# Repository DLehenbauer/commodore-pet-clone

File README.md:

## PET Clone

Open hardware clone of the Commodore CBM/PET using modern parts.
Some assembly required.  :-)

## Status

Working prototype.  PCB and SMT manufacturing files are [here](https://github.com/DLehenbauer/commodore-pet-clone/tree/main/hw/Mainboard/production).

## About

This open hardware CBM/PET clone can be used in two ways:

1. By itself with an HDMI display and USB keyboard
2. As a mainboard replacement to repair/enhance a vintage CBM/PET

You can also do both at once, as shown in the image below:

## Design

The following block diagram provides an overview of the system architecture:

Here are the highlights:

* CPU and I/O are similar to the original Commodore design, using the 6502, PIA, and VIA.
* Main RAM, Display RAM and ROM are combined on a single 128K SRAM.
  * On POR the MCU initializes $9000-FFFF with the user's selected ROM set
  * After initialization, $9000-FFFF is write protected.
* Timing, address decoding, and native PET video are consolidated on a small FPGA.
* The MCU reads display RAM and mirrors the PET video to HDMI (via bit-banged DVI)
* The MCU also reports USB keyboard input to the FPGA
  * The FPGA intercepts reads from $E812 to inject USB key input as-needed
  * When no USB keys are pressed, the read passes through to PIA1.

## Contributing

Collaborators warmly appreciated (see [Issues](https://github.com/DLehenbauer/commodore-pet-clone/issues)).

## License

This project is public domain under the CC0-1.0 license, exempting portions incorporated
from other open source projects as noted [here](NOTICE.md) and in the source code.

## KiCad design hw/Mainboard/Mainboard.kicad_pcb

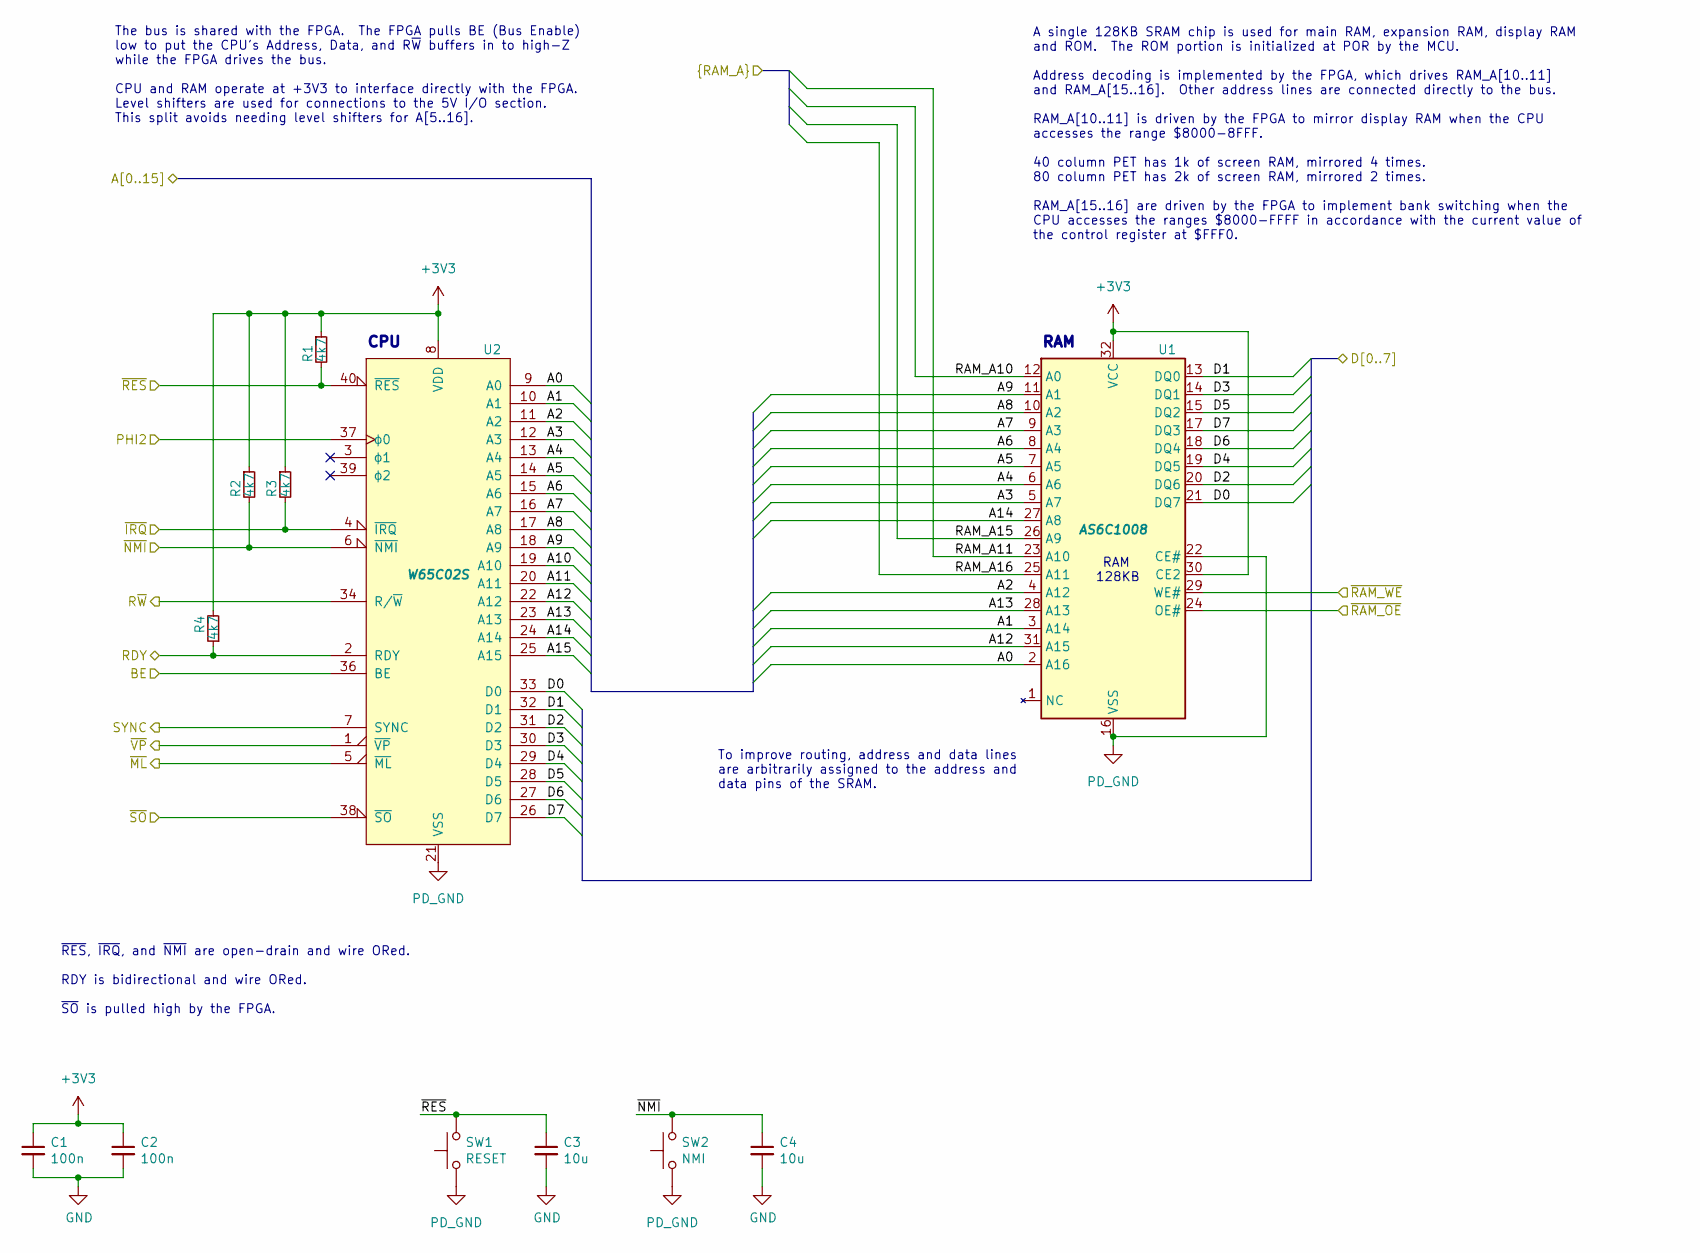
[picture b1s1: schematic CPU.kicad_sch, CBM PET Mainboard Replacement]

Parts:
C1, C2: 100n; C_0402_1005Metric; LCSC C307331
C3, C4: 10u; C_0603_1608Metric; LCSC C96446
R1, R2, R3, R4: 4k7; R_0402_1005Metric; LCSC C25900
SW1: RESET; SW-TH_L6.0-W3.5-P6.50; MOUSER 611-PTS636SK43LFS
SW2: NMI; SW-TH_L6.0-W3.5-P6.50; MOUSER 611-PTS636SK43LFS
U1: AS6C1008; DIP-32_W15.24mm_Socket; MOUSER 913-AS6C1008-55PCN,649-DILB32P223TLF
U2: W65C02S; DIP-40_W15.24mm_Socket; MOUSER 955-W65C02S6TPG-14,571-1-2199299-5

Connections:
+3V3: C1.1, C2.1, R1.1, R2.1, R3.1, R4.2, U1.30 (CE2), U1.32 (VCC), U2.8 (VDD); also elsewhere on the board
/CPU \ RAM/A0: U1.2 (A16), U2.9 (A0); also elsewhere on the board
/CPU \ RAM/A1: U1.3 (A14), U2.10 (A1); also elsewhere on the board
/CPU \ RAM/A2: U1.4 (A12), U2.11 (A2); also elsewhere on the board
/CPU \ RAM/A3: U1.5 (A7), U2.12 (A3); also elsewhere on the board
/CPU \ RAM/A4: U1.6 (A6), U2.13 (A4); also elsewhere on the board
/CPU \ RAM/A5: U1.7 (A5), U2.14 (A5); also elsewhere on the board
/CPU \ RAM/A6: U1.8 (A4), U2.15 (A6); also elsewhere on the board
/CPU \ RAM/A7: U1.9 (A3), U2.16 (A7); also elsewhere on the board
/CPU \ RAM/A8: U1.10 (A2), U2.17 (A8); also elsewhere on the board
/CPU \ RAM/A9: U1.11 (A1), U2.18 (A9); also elsewhere on the board
/CPU \ RAM/A10: U2.19 (A10); also elsewhere on the board
/CPU \ RAM/A11: U2.20 (A11); also elsewhere on the board
/CPU \ RAM/A12: U1.31 (A15), U2.22 (A12); also elsewhere on the board
/CPU \ RAM/A13: U1.28 (A13), U2.23 (A13); also elsewhere on the board
/CPU \ RAM/A14: U1.27 (A8), U2.24 (A14); also elsewhere on the board
/CPU \ RAM/A15: U2.25 (A15); also elsewhere on the board
/CPU \ RAM/D0: U1.21 (DQ7), U2.33 (D0); also elsewhere on the board
/CPU \ RAM/D1: U1.13 (DQ0), U2.32 (D1); also elsewhere on the board
/CPU \ RAM/D2: U1.20 (DQ6), U2.31 (D2); also elsewhere on the board
/CPU \ RAM/D3: U1.14 (DQ1), U2.30 (D3); also elsewhere on the board
/CPU \ RAM/D4: U1.19 (DQ5), U2.29 (D4); also elsewhere on the board
/CPU \ RAM/D5: U1.15 (DQ2), U2.28 (D5); also elsewhere on the board
/CPU \ RAM/D6: U1.18 (DQ4), U2.27 (D6); also elsewhere on the board
/CPU \ RAM/D7: U1.17 (DQ3), U2.26 (D7); also elsewhere on the board
/CPU \ RAM/RAM_A10: U1.12 (A0); also elsewhere on the board
/CPU \ RAM/RAM_A11: U1.23 (A10); also elsewhere on the board
/CPU \ RAM/RAM_A15: U1.26 (A9); also elsewhere on the board
/CPU \ RAM/RAM_A16: U1.25 (A11); also elsewhere on the board
/CPU \ RAM/~NMI: C4.1, R2.2, SW2.2, U2.6 (~NMI); also elsewhere on the board
/CPU \ RAM/~RES: C3.1, R1.2, SW1.2, U2.40 (~RES); also elsewhere on the board
/MAGIC/FPGA/BE: U2.36 (BE); also elsewhere on the board
/MAGIC/FPGA/RDY: R4.1, U2.2 (RDY); also elsewhere on the board
/MAGIC/FPGA/SYNC: U2.7 (SYNC); also elsewhere on the board
/MAGIC/FPGA/~IRQ: R3.2, U2.4 (~IRQ); also elsewhere on the board
/MAGIC/FPGA/~ML: U2.5 (~ML); also elsewhere on the board
/MAGIC/FPGA/~RAM_OE: U1.24 (OE#); also elsewhere on the board
/MAGIC/FPGA/~RAM_WE: U1.29 (WE#); also elsewhere on the board
/MAGIC/FPGA/~SO: U2.38 (~SO); also elsewhere on the board
/MAGIC/FPGA/~VP: U2.1 (~VP); also elsewhere on the board
/MAGIC/PHI2: U2.37 (ϕ0); also elsewhere on the board
/MAGIC/R~W: U2.34 (R/~W); also elsewhere on the board
GND: C1.2, C2.2, C3.2, C4.2; also elsewhere on the board
PD_GND: SW1.1, SW2.1, U1.16 (VSS), U1.22 (CE#), U2.21 (VSS); also elsewhere on the board

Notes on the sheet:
RAM
A single 128KB SRAM chip is used for main RAM, expansion RAM, display RAM and ROM. The ROM portion is initialized at POR by the MCU. Address decoding is implemented by the FPGA, which drives RAM_A[10..11] and RAM_A[15..16]. Other address lines are connected directly to the bus. RAM_A[10..11] is dri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
To improve routing, address and data lines are arbitrarily assigned to the address and data pins of the SRAM.
~{RES}, ~{IRQ}, and ~{NMI} are open-drain and wire ORed. RDY is bidirectional and wire ORed. ~{SO} is pulled high by the FPGA.
RAM 128KB
CPU
The bus is shared with the FPGA. The FPGA pulls BE (Bus Enable) low to put the CPU's Address, Data, and R~{W} buffers in to high-Z while the FPGA drives the bus. CPU and RAM operate at +3V3 to interface directly with the FPGA. Level shifters are used for connections to the 5V I/O section. This spli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

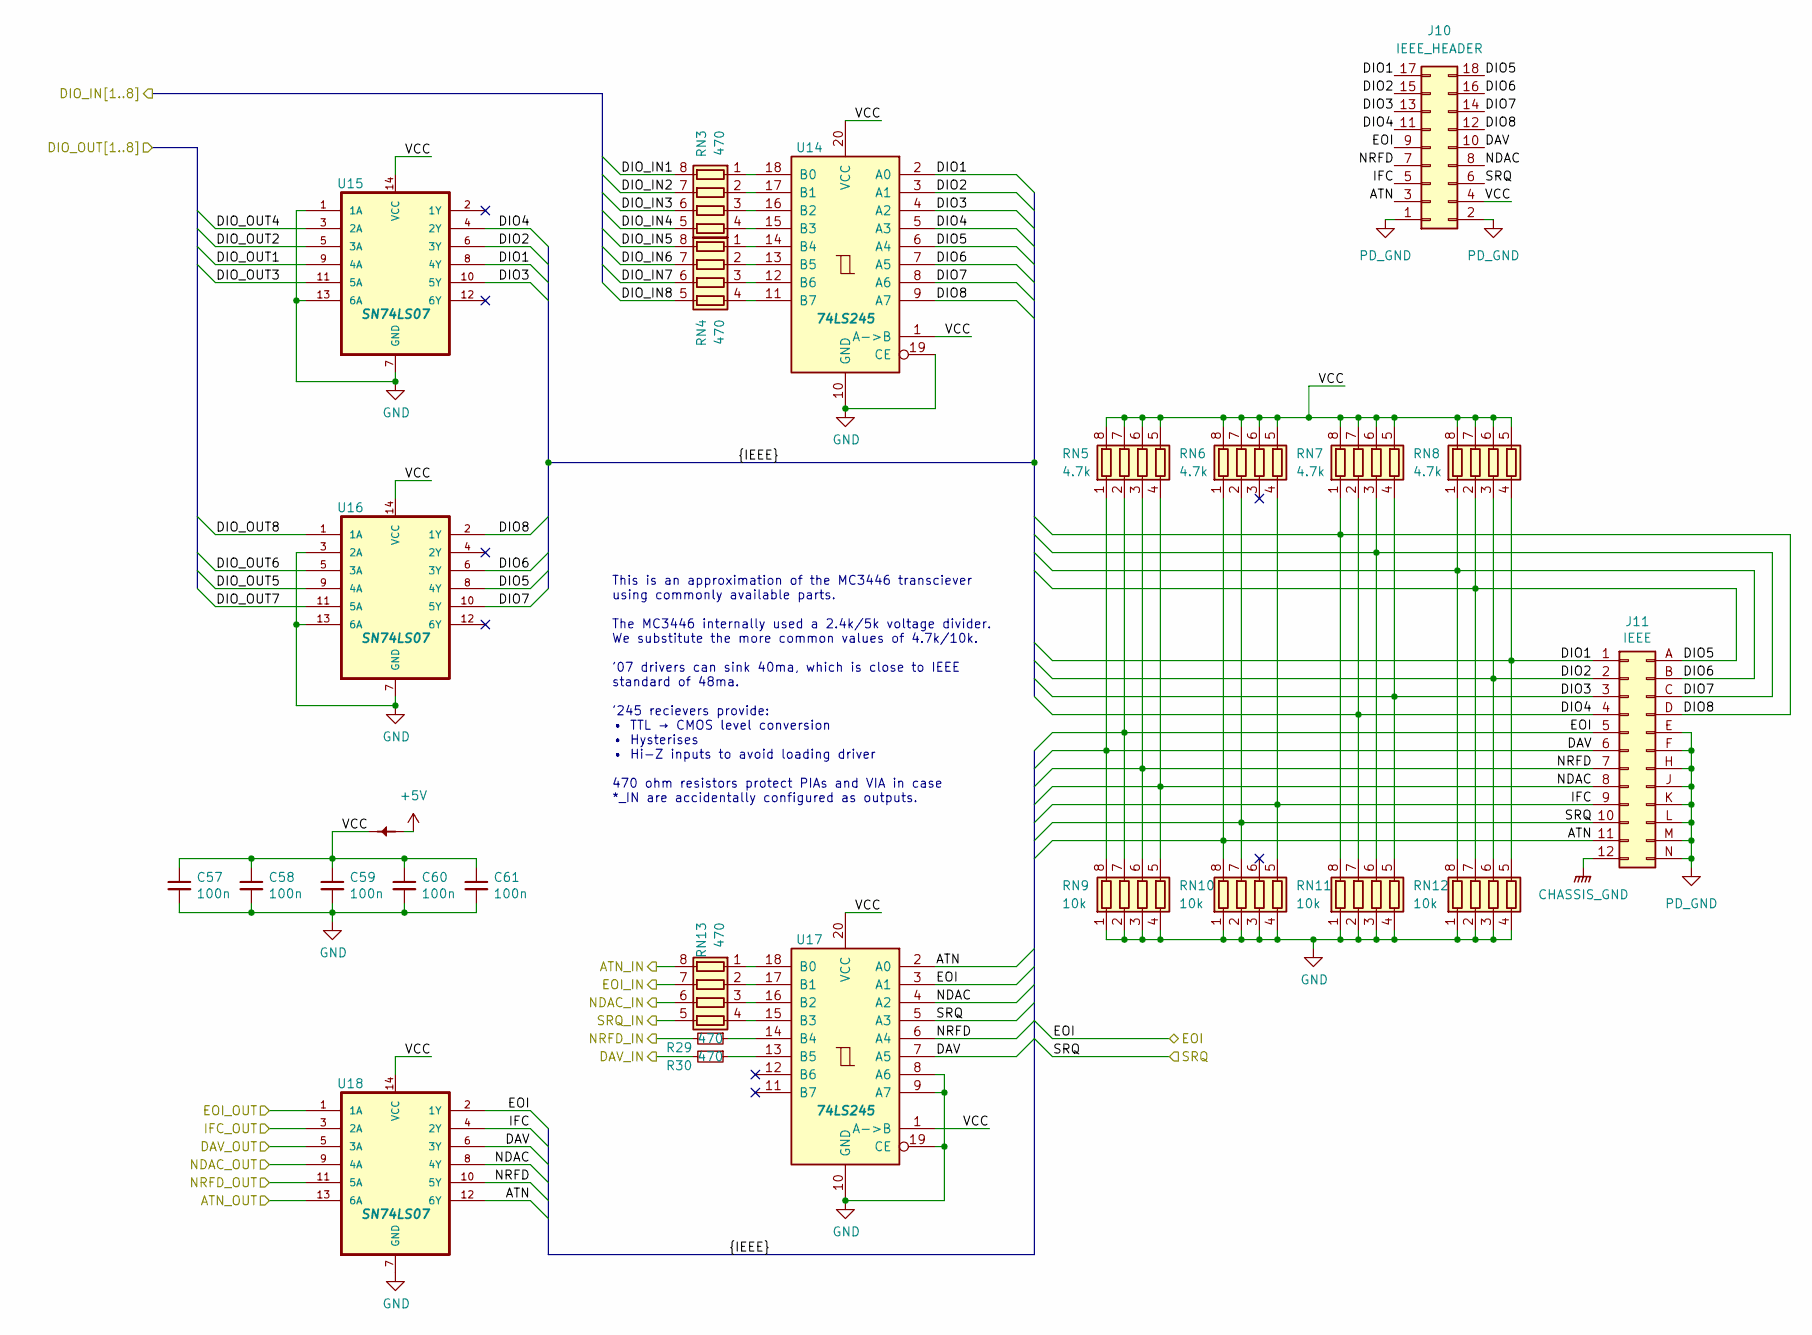
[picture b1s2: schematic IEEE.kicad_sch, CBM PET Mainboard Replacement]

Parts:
C57, C58, C59, C60, C61: 100n; C_0402_1005Metric; LCSC C307331
J10: IEEE_HEADER; PinHeader_2x09_P2.54mm_Vertical; MOUSER 649-1012938195002BLF
J11: IEEE; CBM_PET_IEEE_EDGE_CON_24P
PT36: PowerTie_2; NetTie-2_SMD_Pad_1.6_to_0.4mm
R29, R30: 470; R_0402_1005Metric; LCSC C25117
RN3, RN4, RN13: 470; R_Array_Convex_4x0603; LCSC C25510
RN5, RN6, RN7, RN8: 4.7k; R_Array_Convex_4x0603; LCSC C1980
RN9, RN10, RN11, RN12: 10k; R_Array_Convex_4x0603; LCSC C29718
U14, U17: 74LS245; SOIC-20W_7.5x12.8mm_P1.27mm; LCSC C129580
U15, U16, U18: SN74LS07; SOIC-14_3.9x8.7mm_P1.27mm; LCSC C513513

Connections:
+5V: PT36.1; also elsewhere on the board
/IEEE/ATN: J10.3, J11.11 (ATN), RN6.1 (R1.1), RN10.8 (R1.2), U17.2 (A0), U18.12 (6Y)
/IEEE/ATN_IN: RN13.8 (R1.2); also elsewhere on the board
/IEEE/ATN_OUT: U18.13 (6A); also elsewhere on the board
/IEEE/DAV: J10.10, J11.6 (DAV), RN5.1 (R1.1), RN9.8 (R1.2), U17.7 (A5), U18.6 (3Y)
/IEEE/DAV_IN: R30.2; also elsewhere on the board
/IEEE/DAV_OUT: U18.5 (3A); also elsewhere on the board
/IEEE/DIO1: J10.17, J11.1 (DIO1), RN8.4 (R4.1), RN12.5 (R4.2), U14.2 (A0), U15.8 (4Y)
/IEEE/DIO2: J10.15, J11.2 (DIO2), RN8.3 (R3.1), RN12.6 (R3.2), U14.3 (A1), U15.6 (3Y)
/IEEE/DIO3: J10.13, J11.3 (DIO3), RN7.4 (R4.1), RN11.5 (R4.2), U14.4 (A2), U15.10 (5Y)
/IEEE/DIO4: J10.11, J11.4 (DIO4), RN7.2 (R2.1), RN11.7 (R2.2), U14.5 (A3), U15.4 (2Y)
/IEEE/DIO5: J10.18, J11.A (DIO5), RN8.2 (R2.1), RN12.7 (R2.2), U14.6 (A4), U16.8 (4Y)
/IEEE/DIO6: J10.16, J11.B (DIO6), RN8.1 (R1.1), RN12.8 (R1.2), U14.7 (A5), U16.6 (3Y)
/IEEE/DIO7: J10.14, J11.C (DIO7), RN7.3 (R3.1), RN11.6 (R3.2), U14.8 (A6), U16.10 (5Y)
/IEEE/DIO8: J10.12, J11.D (DIO8), RN7.1 (R1.1), RN11.8 (R1.2), U14.9 (A7), U16.2 (1Y)
/IEEE/DIO_IN1: RN3.8 (R1.2); also elsewhere on the board
/IEEE/DIO_IN2: RN3.7 (R2.2); also elsewhere on the board
/IEEE/DIO_IN3: RN3.6 (R3.2); also elsewhere on the board
/IEEE/DIO_IN4: RN3.5 (R4.2); also elsewhere on the board
/IEEE/DIO_IN5: RN4.8 (R1.2); also elsewhere on the board
/IEEE/DIO_IN6: RN4.7 (R2.2); also elsewhere on the board
/IEEE/DIO_IN7: RN4.6 (R3.2); also elsewhere on the board
/IEEE/DIO_IN8: RN4.5 (R4.2); also elsewhere on the board
/IEEE/DIO_OUT1: U15.9 (4A); also elsewhere on the board
/IEEE/DIO_OUT2: U15.5 (3A); also elsewhere on the board
/IEEE/DIO_OUT3: U15.11 (5A); also elsewhere on the board
/IEEE/DIO_OUT4: U15.3 (2A); also elsewhere on the board
/IEEE/DIO_OUT5: U16.9 (4A); also elsewhere on the board
/IEEE/DIO_OUT6: U16.5 (3A); also elsewhere on the board
/IEEE/DIO_OUT7: U16.11 (5A); also elsewhere on the board
/IEEE/DIO_OUT8: U16.1 (1A); also elsewhere on the board
/IEEE/EOI: J10.9, J11.5 (EOI), RN5.2 (R2.1), RN9.7 (R2.2), U17.3 (A1), U18.2 (1Y); also elsewhere on the board
/IEEE/EOI_IN: RN13.7 (R2.2); also elsewhere on the board
/IEEE/EOI_OUT: U18.1 (1A); also elsewhere on the board
/IEEE/IFC: J10.5, J11.9 (IFC), RN6.4 (R4.1), RN10.5 (R4.2), U18.4 (2Y)
/IEEE/IFC_OUT: U18.3 (2A); also elsewhere on the board
/IEEE/NDAC: J10.8, J11.8 (NDAC), RN5.4 (R4.1), RN9.5 (R4.2), U17.4 (A2), U18.8 (4Y)
/IEEE/NDAC_IN: RN13.6 (R3.2); also elsewhere on the board
/IEEE/NDAC_OUT: U18.9 (4A); also elsewhere on the board
/IEEE/NRFD: J10.7, J11.7 (NRFD), RN5.3 (R3.1), RN9.6 (R3.2), U17.6 (A4), U18.10 (5Y)
/IEEE/NRFD_IN: R29.2; also elsewhere on the board
/IEEE/NRFD_OUT: U18.11 (5A); also elsewhere on the board
/IEEE/SRQ: J10.6, J11.10 (SRQ), RN6.2 (R2.1), RN10.7 (R2.2), U17.5 (A3); also elsewhere on the board
/IEEE/SRQ_IN: RN13.5 (R4.2); also elsewhere on the board
/IEEE/VCC: C57.1, C58.1, C59.1, C60.1, C61.1, J10.4, PT36.2, RN5.5 (R4.2), RN5.6 (R3.2), RN5.7 (R2.2), RN5.8 (R1.2), RN6.5 (R4.2), RN6.6 (R3.2), RN6.7 (R2.2), RN6.8 (R1.2), RN7.5 (R4.2), RN7.6 (R3.2), RN7.7 (R2.2), RN7.8 (R1.2), RN8.5 (R4.2), RN8.6 (R3.2), RN8.7 (R2.2), RN8.8 (R1.2), U14.1 (A->B), U14.20 (VCC), U15.14 (VCC), U16.14 (VCC), U17.1 (A->B), U17.20 (VCC), U18.14 (VCC)
CHASSIS_GND: J11.12 (GND); also elsewhere on the board
GND: C57.2, C58.2, C59.2, C60.2, C61.2, RN9.1 (R1.1), RN9.2 (R2.1), RN9.3 (R3.1), RN9.4 (R4.1), RN10.1 (R1.1), RN10.2 (R2.1), RN10.3 (R3.1), RN10.4 (R4.1), RN11.1 (R1.1), RN11.2 (R2.1), RN11.3 (R3.1), RN11.4 (R4.1), RN12.1 (R1.1), RN12.2 (R2.1), RN12.3 (R3.1), RN12.4 (R4.1), U14.10 (GND), U14.19 (CE), U15.1 (1A), U15.7 (GND), U15.13 (6A), U16.3 (2A), U16.7 (GND), U16.13 (6A), U17.8 (A6), U17.9 (A7), U17.10 (GND), U17.19 (CE), U18.7 (GND); also elsewhere on the board
unnamed: R29.1, U17.14 (B4)
unnamed: R30.1, U17.13 (B5)
unnamed: RN3.1 (R1.1), U14.18 (B0)
unnamed: RN3.2 (R2.1), U14.17 (B1)
unnamed: RN3.3 (R3.1), U14.16 (B2)
unnamed: RN3.4 (R4.1), U14.15 (B3)
unnamed: RN4.1 (R1.1), U14.14 (B4)
unnamed: RN4.2 (R2.1), U14.13 (B5)
unnamed: RN4.3 (R3.1), U14.12 (B6)
unnamed: RN4.4 (R4.1), U14.11 (B7)
unnamed: RN13.1 (R1.1), U17.18 (B0)
unnamed: RN13.2 (R2.1), U17.17 (B1)
unnamed: RN13.3 (R3.1), U17.16 (B2)
unnamed: RN13.4 (R4.1), U17.15 (B3)
PD_GND: J10.1, J10.2, J11.E (GND), J11.F (GND), J11.H (GND), J11.J (GND), J11.K (GND), J11.L (GND), J11.M (GND), J11.N (GND); also elsewhere on the board

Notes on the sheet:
This is an approximation of the MC3446 transciever using commonly available parts. The MC3446 internally used a 2.4k/5k voltage divider. We substitute the more common values of 4.7k/10k. '07 drivers can sink 40ma, which is close to IEEE standard of 48ma. '245 recievers provide: • TTL → CMOS level c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

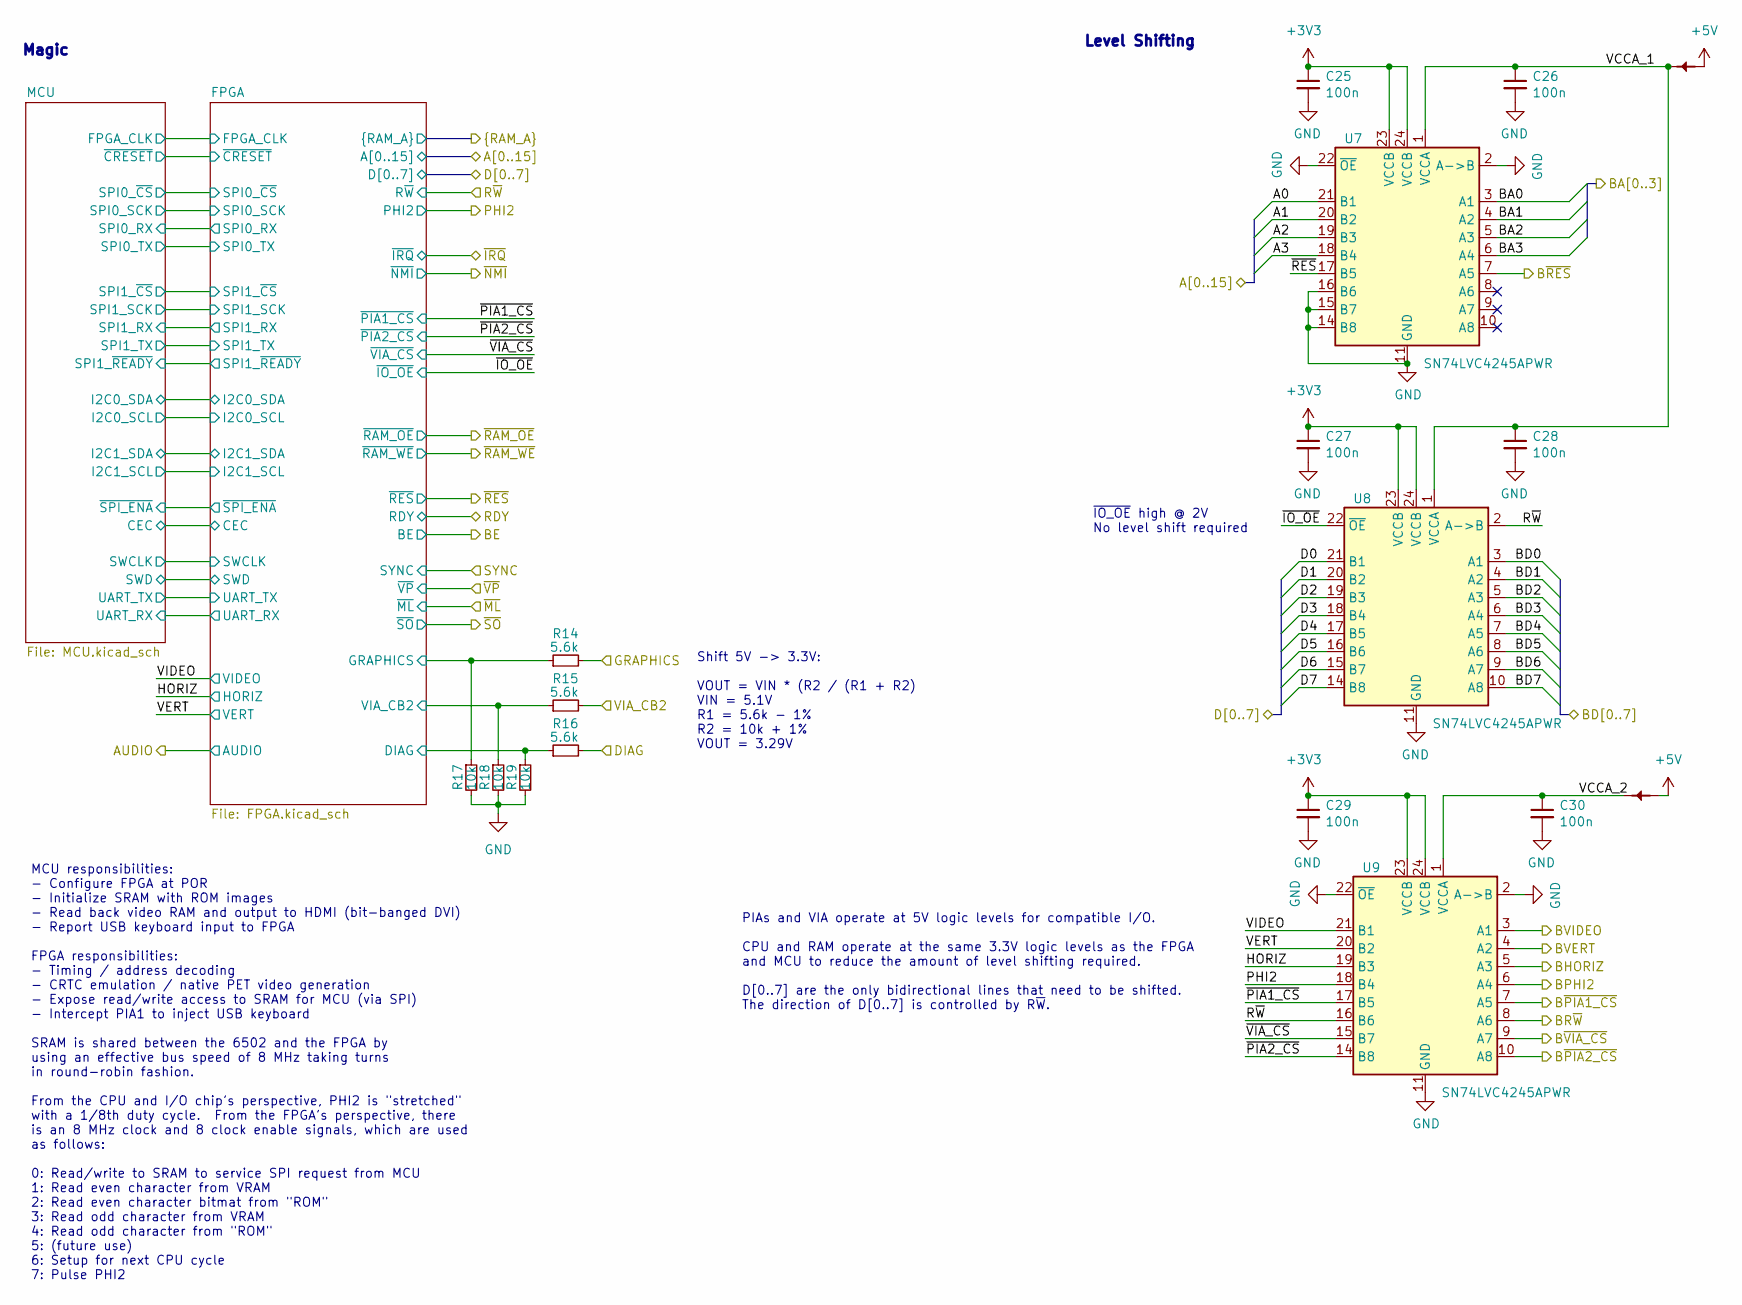
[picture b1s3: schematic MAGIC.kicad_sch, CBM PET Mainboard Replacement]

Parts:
C25, C26, C27, C28, C29, C30: 100n; C_0402_1005Metric; LCSC C307331
PT13, PT14: PowerTie_2; NetTie-2_SMD_Pad_1.6_to_0.4mm
R14, R15, R16: 5.6k; R_0402_1005Metric; LCSC C25908
R17, R18, R19: 10k; R_0402_1005Metric; LCSC C25744
U7, U8, U9: SN74LVC4245APWR; TSSOP-24_4.4x7.8mm_P0.65mm; LCSC C7859

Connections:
+3V3: C25.1, C27.1, C29.1, U7.23 (VCCB), U7.24 (VCCB), U8.23 (VCCB), U8.24 (VCCB), U9.23 (VCCB), U9.24 (VCCB); also elsewhere on the board
+5V: PT13.1, PT14.1; also elsewhere on the board
/CPU \ RAM/A0: U7.21 (B1); also elsewhere on the board
/CPU \ RAM/A1: U7.20 (B2); also elsewhere on the board
/CPU \ RAM/A2: U7.19 (B3); also elsewhere on the board
/CPU \ RAM/A3: U7.18 (B4); also elsewhere on the board
/CPU \ RAM/D0: U8.21 (B1); also elsewhere on the board
/CPU \ RAM/D1: U8.20 (B2); also elsewhere on the board
/CPU \ RAM/D2: U8.19 (B3); also elsewhere on the board
/CPU \ RAM/D3: U8.18 (B4); also elsewhere on the board
/CPU \ RAM/D4: U8.17 (B5); also elsewhere on the board
/CPU \ RAM/D5: U8.16 (B6); also elsewhere on the board
/CPU \ RAM/D6: U8.15 (B7); also elsewhere on the board
/CPU \ RAM/D7: U8.14 (B8); also elsewhere on the board
/CPU \ RAM/~RES: U7.17 (B5); also elsewhere on the board
/IEEE/IFC_OUT: U7.7 (A5); also elsewhere on the board
/IO/BA0: U7.3 (A1); also elsewhere on the board
/IO/BA1: U7.4 (A2); also elsewhere on the board
/IO/BA2: U7.5 (A3); also elsewhere on the board
/IO/BA3: U7.6 (A4); also elsewhere on the board
/IO/BD0: U8.3 (A1); also elsewhere on the board
/IO/BD1: U8.4 (A2); also elsewhere on the board
/IO/BD2: U8.5 (A3); also elsewhere on the board
/IO/BD3: U8.6 (A4); also elsewhere on the board
/IO/BD4: U8.7 (A5); also elsewhere on the board
/IO/BD5: U8.8 (A6); also elsewhere on the board
/IO/BD6: U8.9 (A7); also elsewhere on the board
/IO/BD7: U8.10 (A8); also elsewhere on the board
/IO/BPHI2: U9.6 (A4); also elsewhere on the board
/IO/BR~W: U9.8 (A6); also elsewhere on the board
/IO/BVERT: U9.4 (A2); also elsewhere on the board
/IO/B~PIA1_CS: U9.7 (A5); also elsewhere on the board
/IO/B~PIA2_CS: U9.10 (A8); also elsewhere on the board
/IO/B~VIA_CS: U9.9 (A7); also elsewhere on the board
/IO/DIAG: R16.2; also elsewhere on the board
/IO/GRAPHIC: R14.2; also elsewhere on the board
/IO/VIA_CB2: R15.2; also elsewhere on the board
/MAGIC/BHORIZ: U9.5 (A3); also elsewhere on the board
/MAGIC/BVIDEO: U9.3 (A1); also elsewhere on the board
/MAGIC/FPGA/DIAG: R16.1, R19.1; also elsewhere on the board
/MAGIC/FPGA/GRAPHICS: R14.1, R17.1; also elsewhere on the board
/MAGIC/FPGA/VIA_CB2: R15.1, R18.1; also elsewhere on the board
/MAGIC/HORIZ: U9.19 (B3); also elsewhere on the board
/MAGIC/PHI2: U9.18 (B4); also elsewhere on the board
/MAGIC/R~W: U8.2 (A->B), U9.16 (B6); also elsewhere on the board
/MAGIC/VCCA_1: C26.1, C28.1, PT13.2, U7.1 (VCCA), U8.1 (VCCA)
/MAGIC/VCCA_2: C30.1, PT14.2, U9.1 (VCCA)
/MAGIC/VERT: U9.20 (B2); also elsewhere on the board
/MAGIC/VIDEO: U9.21 (B1); also elsewhere on the board
/MAGIC/~IO_OE: U8.22 (~OE); also elsewhere on the board
/MAGIC/~PIA1_CS: U9.17 (B5); also elsewhere on the board
/MAGIC/~PIA2_CS: U9.14 (B8); also elsewhere on the board
/MAGIC/~VIA_CS: U9.15 (B7); also elsewhere on the board
GND: C25.2, C26.2, C27.2, C28.2, C29.2, C30.2, R17.2, R18.2, R19.2, U7.2 (A->B), U7.11 (GND), U7.12 (GND), U7.13 (GND), U7.14 (B8), U7.15 (B7), U7.16 (B6), U7.22 (~OE), U8.11 (GND), U8.12 (GND), U8.13 (GND), U9.2 (A->B), U9.11 (GND), U9.12 (GND), U9.13 (GND), U9.22 (~OE); also elsewhere on the board

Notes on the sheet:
PIAs and VIA operate at 5V logic levels for compatible I/O. CPU and RAM operate at the same 3.3V logic levels as the FPGA and MCU to reduce the amount of level shifting required. D[0..7] are the only bidirectional lines that need to be shifted. The direction of D[0..7] is controlled by R~{W}.
Level Shifting
Magic
MCU responsibilities: - Configure FPGA at POR - Initialize SRAM with ROM images - Read back video RAM and output to HDMI (bit-banged DVI) - Report USB keyboard input to FPGA FPGA responsibilities: - Timing / address decoding - CRTC emulation / native PET video generation - Expose read/write access 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
~{IO_OE} high @ 2V No level shift required
Shift 5V -> 3.3V: VOUT = VIN * (R2 / (R1 + R2) VIN = 5.1V R1 = 5.6k - 1% R2 = 10k + 1% VOUT = 3.29V

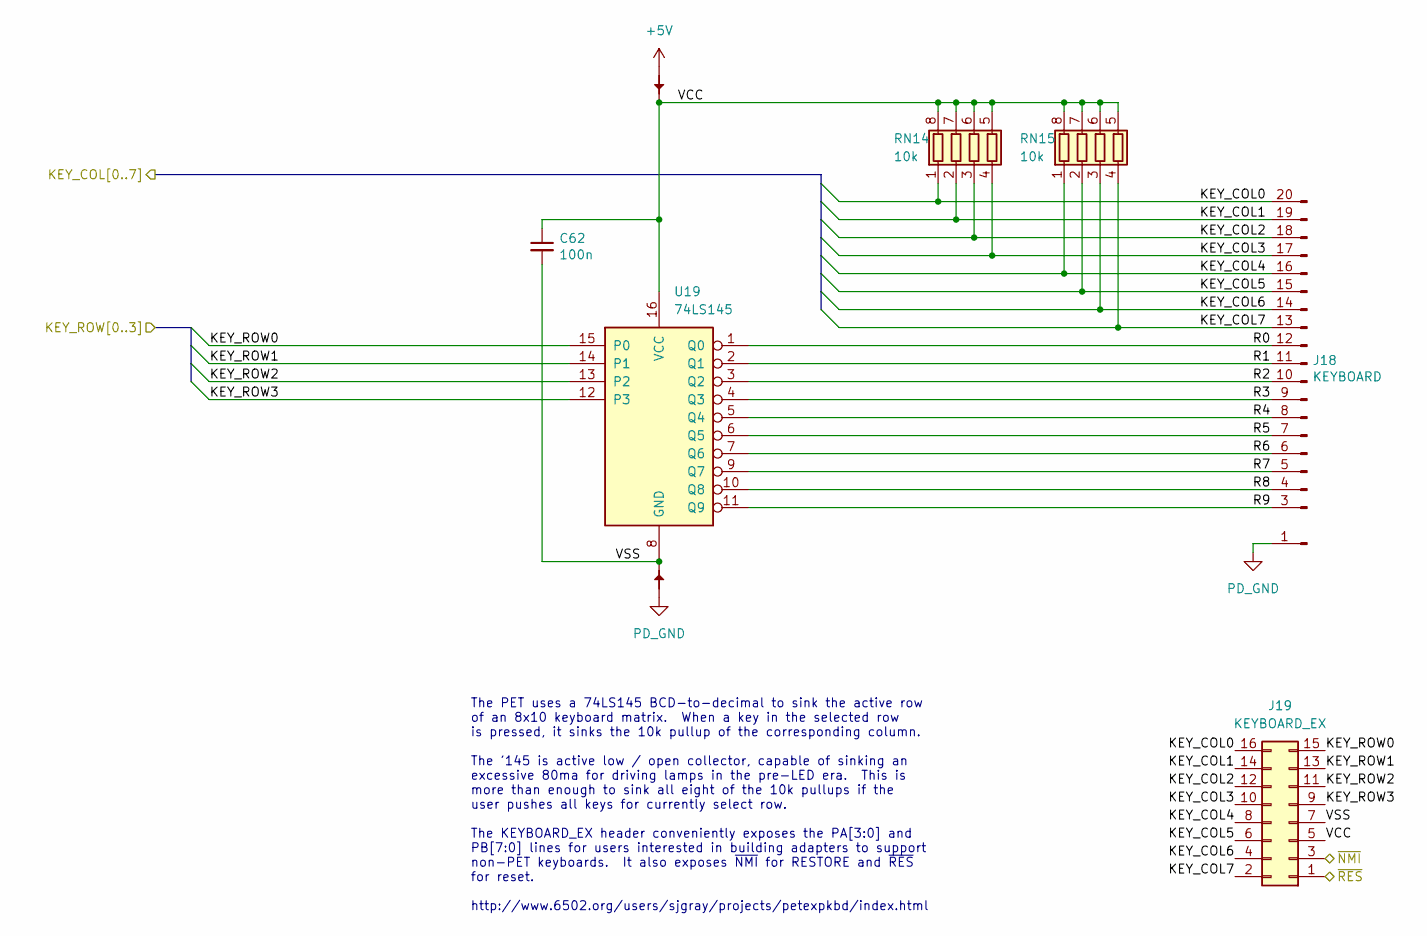
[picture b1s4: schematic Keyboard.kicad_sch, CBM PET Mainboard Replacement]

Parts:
C62: 100n; C_0402_1005Metric; LCSC C307331
J18: KEYBOARD; CBM_PET_KEYBOARD_KEYED_20P; MPN 2-826646-0; MOUSER 649-1012937893603BLF
J19: KEYBOARD_EX; PinHeader_2x08_P2.54mm_Vertical; MOUSER 649-1012938195002BLF
PT42, PT43: PowerTie_2; NetTie-2_SMD_Pad_1.6_to_0.4mm
RN14, RN15: 10k; R_Array_Convex_4x0603; LCSC C29718
U19: 74LS145; SOIC-16_3.9x9.9mm_P1.27mm; LCSC C60829

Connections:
+5V: PT42.1; also elsewhere on the board
/CPU \ RAM/~NMI: J19.3; also elsewhere on the board
/CPU \ RAM/~RES: J19.1; also elsewhere on the board
/IO/KEY_COL0: J18.20, J19.16, RN14.1 (R1.1); also elsewhere on the board
/IO/KEY_COL1: J18.19, J19.14, RN14.2 (R2.1); also elsewhere on the board
/IO/KEY_COL2: J18.18, J19.12, RN14.3 (R3.1); also elsewhere on the board
/IO/KEY_COL3: J18.17, J19.10, RN14.4 (R4.1); also elsewhere on the board
/IO/KEY_COL4: J18.16, J19.8, RN15.1 (R1.1); also elsewhere on the board
/IO/KEY_COL5: J18.15, J19.6, RN15.2 (R2.1); also elsewhere on the board
/IO/KEY_COL6: J18.14, J19.4, RN15.3 (R3.1); also elsewhere on the board
/IO/KEY_COL7: J18.13, J19.2, RN15.4 (R4.1); also elsewhere on the board
/IO/KEY_ROW0: J19.15, U19.15 (P0); also elsewhere on the board
/IO/KEY_ROW1: J19.13, U19.14 (P1); also elsewhere on the board
/IO/KEY_ROW2: J19.11, U19.13 (P2); also elsewhere on the board
/IO/KEY_ROW3: J19.9, U19.12 (P3); also elsewhere on the board
/Keyboard/R0: J18.12, U19.1 (Q0)
/Keyboard/R1: J18.11, U19.2 (Q1)
/Keyboard/R2: J18.10, U19.3 (Q2)
/Keyboard/R3: J18.9, U19.4 (Q3)
/Keyboard/R4: J18.8, U19.5 (Q4)
/Keyboard/R5: J18.7, U19.6 (Q5)
/Keyboard/R6: J18.6, U19.7 (Q6)
/Keyboard/R7: J18.5, U19.9 (Q7)
/Keyboard/R8: J18.4, U19.10 (Q8)
/Keyboard/R9: J18.3, U19.11 (Q9)
/Keyboard/VCC: C62.1, J19.5, PT42.2, RN14.5 (R4.2), RN14.6 (R3.2), RN14.7 (R2.2), RN14.8 (R1.2), RN15.5 (R4.2), RN15.6 (R3.2), RN15.7 (R2.2), RN15.8 (R1.2), U19.16 (VCC)
/Keyboard/VSS: C62.2, J19.7, PT43.2, U19.8 (GND)
PD_GND: J18.1, PT43.1; also elsewhere on the board

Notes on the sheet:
The PET uses a 74LS145 BCD-to-decimal to sink the active row of an 8x10 keyboard matrix. When a key in the selected row is pressed, it sinks the 10k pullup of the corresponding column. The '145 is active low / open collector, capable of sinking an excessive 80ma for driving lamps in the pre-LED era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

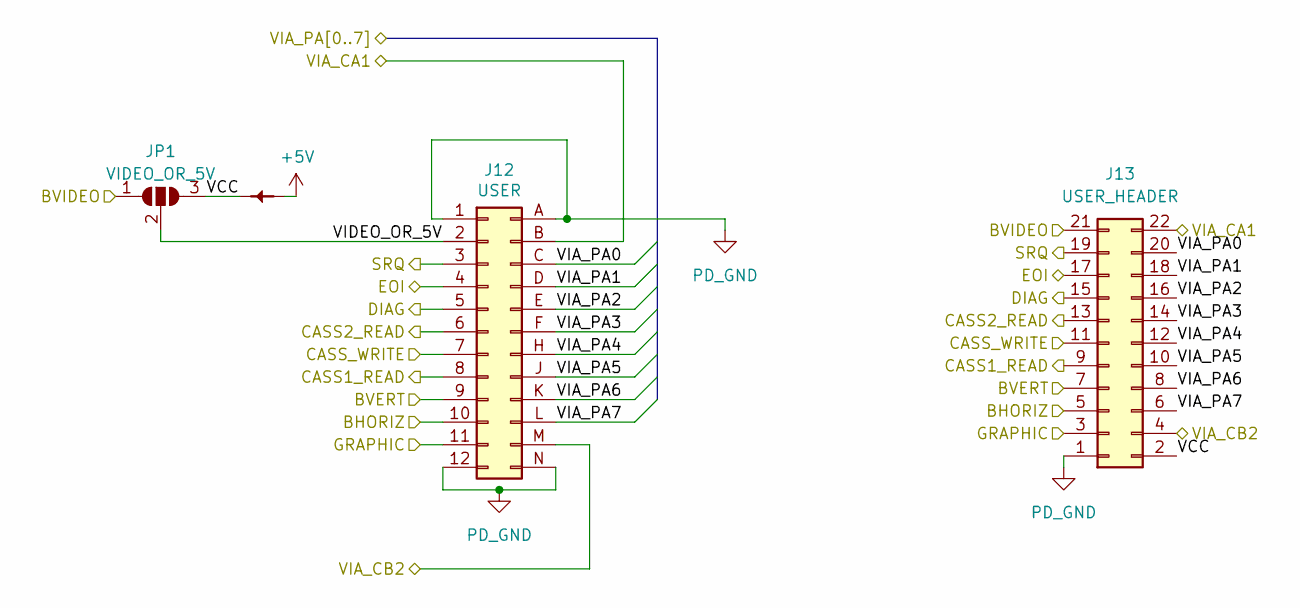
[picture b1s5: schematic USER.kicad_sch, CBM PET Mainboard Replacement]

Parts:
J12: USER; CBM_PET_USER_EDGE_CON_24P
J13: USER_HEADER; PinHeader_2x11_P2.54mm_Vertical; MOUSER 649-1012938195002BLF
JP1: VIDEO_OR_5V; PinHeader_and_Jumper_1x03_P2.54mm_Vertical
PT37: PowerTie_2; NetTie-2_SMD_Pad_1.6_to_0.4mm

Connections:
+5V: PT37.1; also elsewhere on the board
/CASS/CASS1_READ: J12.8 (CASS1_READ), J13.9; also elsewhere on the board
/CASS/CASS2_READ: J12.6 (CASS2_READ), J13.13; also elsewhere on the board
/CASS/CASS_WRITE: J12.7 (CASS_WRITE), J13.11; also elsewhere on the board
/IEEE/EOI: J12.4 (EOI), J13.17; also elsewhere on the board
/IEEE/SRQ: J12.3 (SRQ), J13.19; also elsewhere on the board
/IO/BVERT: J12.9 (VERT), J13.7; also elsewhere on the board
/IO/DIAG: J12.5 (DIAG), J13.15; also elsewhere on the board
/IO/GRAPHIC: J12.11 (GRAPHIC), J13.3; also elsewhere on the board
/IO/VIA_CA1: J12.B (VIA_CA1), J13.22; also elsewhere on the board
/IO/VIA_CB2: J12.M (VIA_CB2), J13.4; also elsewhere on the board
/IO/VIA_PA0: J12.C (VIA_PA0), J13.20; also elsewhere on the board
/IO/VIA_PA1: J12.D (VIA_PA1), J13.18; also elsewhere on the board
/IO/VIA_PA2: J12.E (VIA_PA2), J13.16; also elsewhere on the board
/IO/VIA_PA3: J12.F (VIA_PA3), J13.14; also elsewhere on the board
/IO/VIA_PA4: J12.H (VIA_PA4), J13.12; also elsewhere on the board
/IO/VIA_PA5: J12.J (VIA_PA5), J13.10; also elsewhere on the board
/IO/VIA_PA6: J12.K (VIA_PA6), J13.8; also elsewhere on the board
/IO/VIA_PA7: J12.L (VIA_PA7), J13.6; also elsewhere on the board
/MAGIC/BHORIZ: J12.10 (HORIZ), J13.5; also elsewhere on the board
/MAGIC/BVIDEO: J13.21, JP1.1 (A); also elsewhere on the board
/USER/VCC: J13.2, JP1.3 (B), PT37.2
/USER/VIDEO_OR_5V: J12.2 (~VIDEO), JP1.2 (C)
PD_GND: J12.1 (GND), J12.12 (GND), J12.A (GND), J12.N (GND), J13.1; also elsewhere on the board

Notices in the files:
sw/src/driver.hpp:
@copyright CC0 http://creativecommons.org/publicdomain/zero/1.0
